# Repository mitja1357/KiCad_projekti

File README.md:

# KiCad_projekti
Tu se trudim sestaviti kaksen PCB :)

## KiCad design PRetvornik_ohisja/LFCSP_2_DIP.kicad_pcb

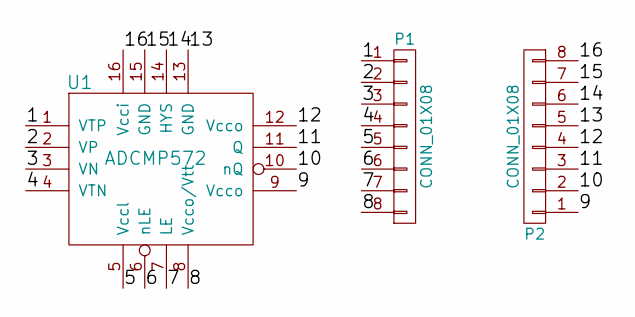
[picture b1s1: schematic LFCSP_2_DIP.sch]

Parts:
P1, P2: CONN_01X08; Socket_Strip_Straight_1x08_Pitch2.54mm
U1: ADCMP572; LFCSP_45

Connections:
/1: P1.1, U1.1 (VTP)
/2: P1.2, U1.2 (VP)
/3: P1.3, U1.3 (VN)
/4: P1.4, U1.4 (VTN)
/5: P1.5, U1.5 (Vccl)
/6: P1.6, U1.6 (nLE)
/7: P1.7, U1.7 (LE)
/8: P1.8, U1.8 (Vcco/Vtt)
/9: P2.1, U1.9 (Vcco)
/10: P2.2, U1.10 (nQ)
/11: P2.3, U1.11 (Q)
/12: P2.4, U1.12 (Vcco)
/13: P2.5, U1.13 (GND)
/14: P2.6, U1.14 (HYS)
/15: P2.7, U1.15 (GND)
/16: P2.8, U1.16 (Vcci)

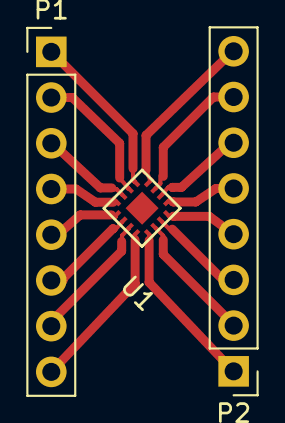
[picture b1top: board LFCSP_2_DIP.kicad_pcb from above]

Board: 2 copper layers, 3 parts (0 on the bottom side), 16 nets.

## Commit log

2017-06-28 Sestavil shemo za vezje s TDA7294 ojacevalnikom
2017-06-29 Narisal pretvornik s LFCSP_2_DIP
2017-06-30 Naredil nov LFCSP s osrednjim padom in ga zavrtel za 45 stopinj
